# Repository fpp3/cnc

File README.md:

# cnc
Trabajo Practico Integrador de 4to año de la carrera Ingeniería Electrónica en la Universidad Tecnológica Nacional, Facultad Regional Córdoba. Materias involucradas: Electrónica Aplicada II, Técnicas Digitales II, Maquinas e Instalaciones Electricas

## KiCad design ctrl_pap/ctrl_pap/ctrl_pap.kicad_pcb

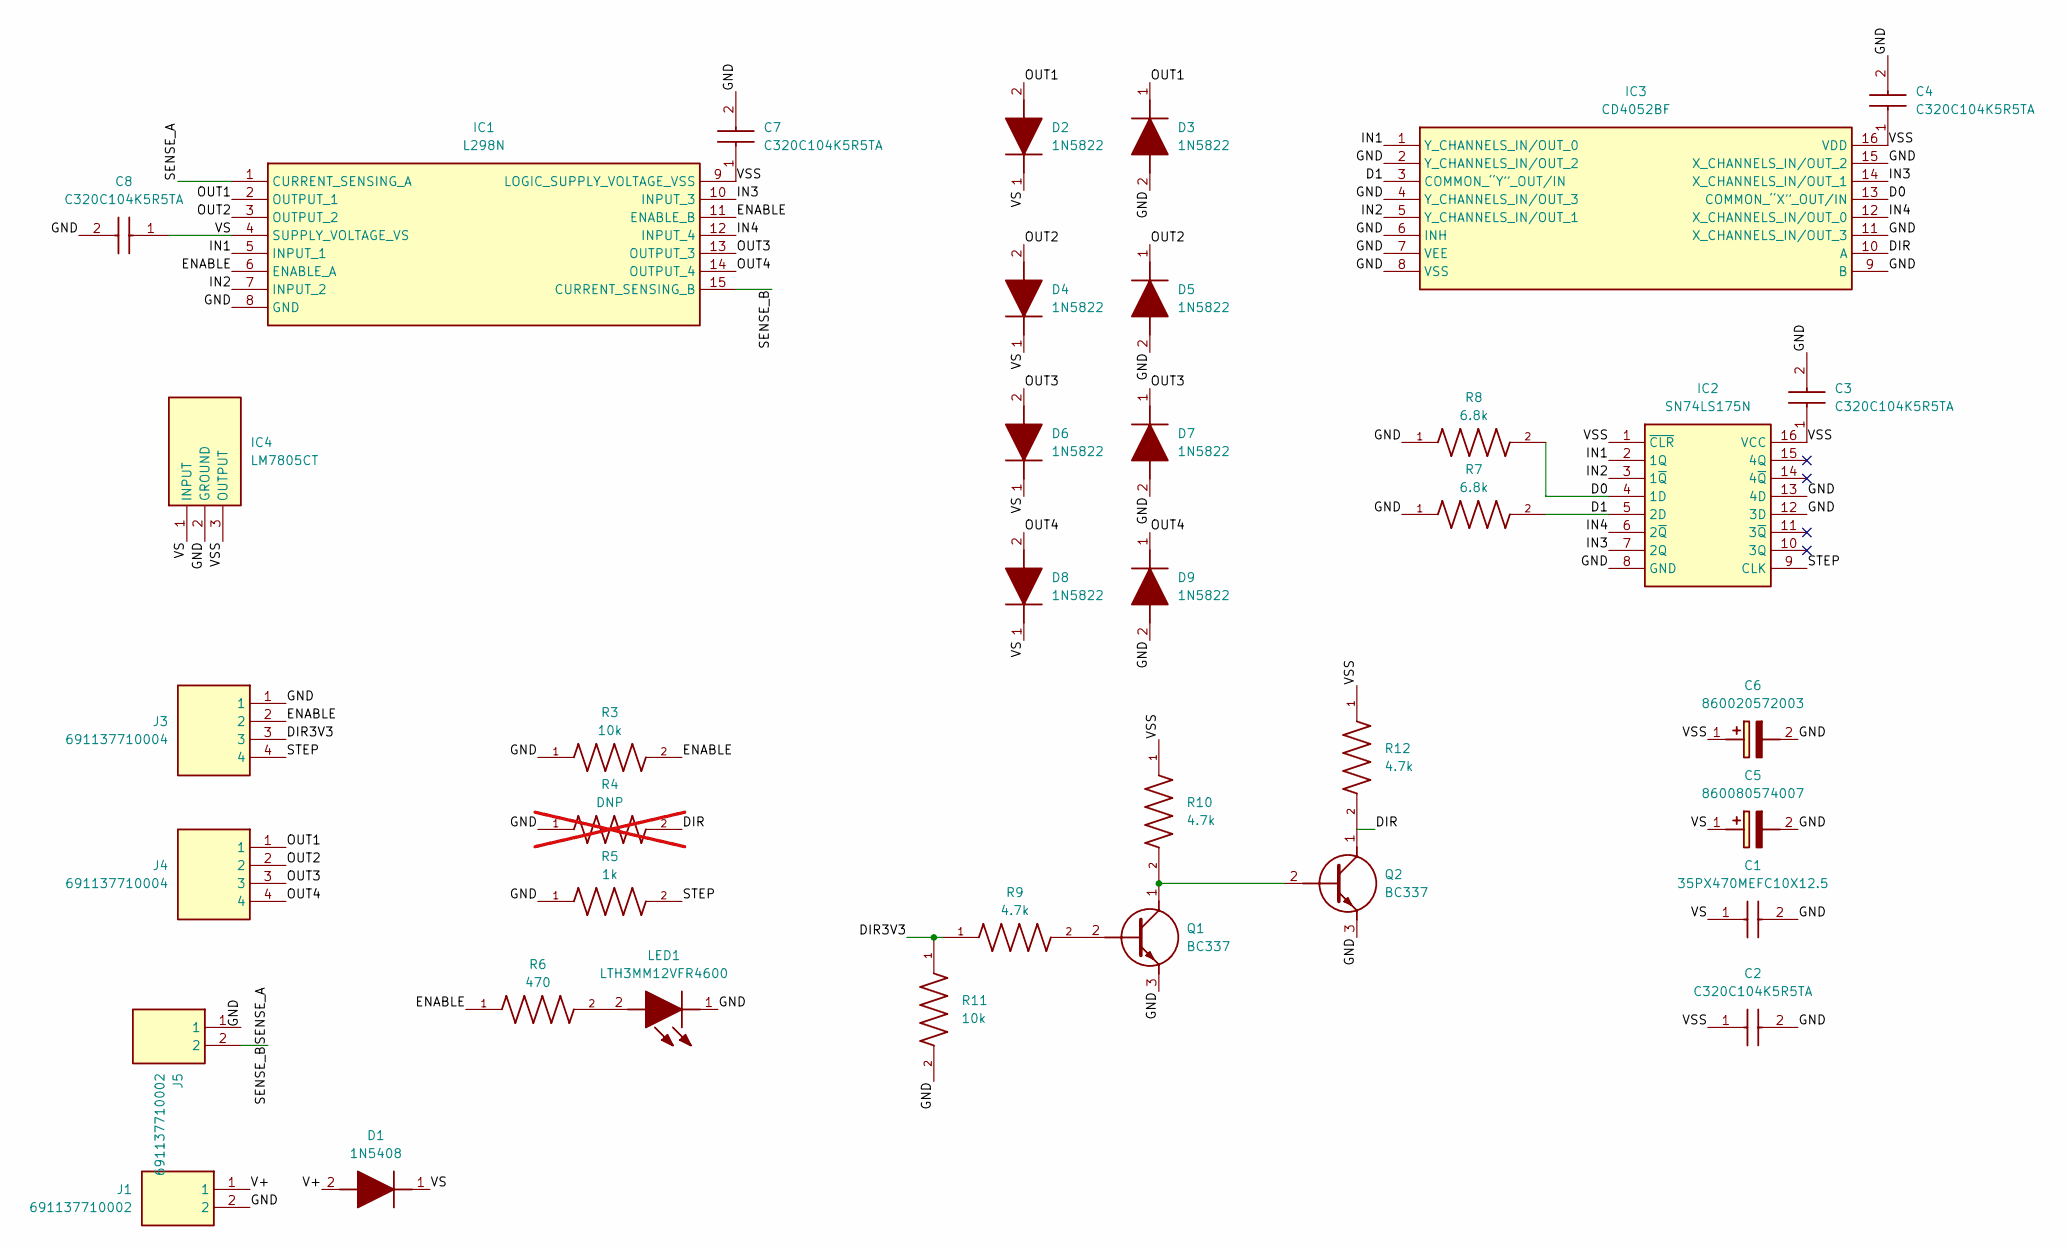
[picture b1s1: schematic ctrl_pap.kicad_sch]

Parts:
C1: 35PX470MEFC10X12.5; CAPPRD500W60D1025H1400; Manufacturer_Part_Number 35PX470MEFC10X12.5; Mouser Part Number 232-35PX470MEFC10X12
C2, C3, C4, C7, C8: C320C104K5R5TA; Manufacturer_Part_Number C320C104K5R5TA; Mouser Part Number 80-C320C104K5R
C5: 860080574007; CAPPRD350W52D800H1300; Manufacturer_Part_Number 860080574007; Mouser Part Number 710-860080574007
C6: 860020572003; CAPPRD200W52D500H1250; Manufacturer_Part_Number 860020572003; Mouser Part Number 710-860020572003
D1: 1N5408; DIOAD2510W125L750D440; Manufacturer_Part_Number 1N5408; Mouser Part Number 637-1N5408
D2, D3, D4, D5, D6, D7, D8, D9: 1N5822; DIOAD3070W130L950D530; Manufacturer_Part_Number 1N5822; Mouser Part Number 512-1N5822
IC1: L298N; TO127P500X2020X2210-15P; Manufacturer_Part_Number L298N; Mouser Part Number 511-L298
IC2: SN74LS175N; DIP794W53P254L1930H508Q16N; Manufacturer_Part_Number SN74LS175N; Mouser Part Number 595-SN74LS175N
IC3: CD4052BF; CDIP762W66P254L2134H508Q16; Manufacturer_Part_Number CD4052BF; Mouser Part Number 595-CD4052BF
IC4: LM7805CT; TO254P470X1028X1955-3P; Manufacturer_Part_Number LM7805CT; Mouser Part Number 926-LM7805CT
J1, J5: 691137710002; SHDR2W70P0X500_1X2_1000X750X1150P; Manufacturer_Part_Number 691137710002; Mouser Part Number 710-691137710002
J3, J4: 691137710004; Manufacturer_Part_Number 691137710004; Mouser Part Number 710-691137710004
LED1: LTH3MM12VFR4600; Manufacturer_Part_Number LTH3MM12VFR4600; Mouser Part Number 593-LTH3MM12VFR4600
Q1, Q2: BC337; Manufacturer_Part_Number BC337
R3, R11: 10k; RESAD1100W55L680D260; PARTREV 201304
R4: DNP; RESAD1100W55L680D260; PARTREV 201304; not fitted
R5: 1k; RESAD1100W55L680D260; PARTREV 201304
R6: 470; RESAD1100W55L680D260; PARTREV 201304
R7, R8: 6.8k; RESAD1100W55L680D260; PARTREV 201304
R9, R10, R12: 4.7k; RESAD1100W55L680D260; PARTREV 201304

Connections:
/D0: IC2.4 (1D), IC3.13 (COMMON_“X”_OUT/IN), R8.2
/D1: IC2.5 (2D), IC3.3 (COMMON_“Y”_OUT/IN), R7.2
/DIR: IC3.10 (A), Q2.1 (C), R4.2, R12.2
/DIR3V3: J3.3, R9.1, R11.1
/ENABLE: IC1.6 (ENABLE_A), IC1.11 (ENABLE_B), J3.2, R3.2, R6.1
/GND: C1.2 (-), C2.2, C3.2, C4.2, C5.2 (-), C6.2 (-), C7.2, C8.2, D3.2 (A), D5.2 (A), D7.2 (A), D9.2 (A), IC1.8 (GND), IC2.8 (GND), IC2.12 (3D), IC2.13 (4D), IC3.2 (Y_CHANNELS_IN/OUT_2), IC3.4 (Y_CHANNELS_IN/OUT_3), IC3.6 (INH), IC3.7 (VEE), IC3.8 (VSS), IC3.9 (B), IC3.11 (X_CHANNELS_IN/OUT_3), IC3.15 (X_CHANNELS_IN/OUT_2), IC4.2 (GROUND), J1.2, J3.1, J5.1, LED1.1 (K), Q1.3 (E), Q2.3 (E), R3.1, R4.1, R5.1, R7.1, R8.1, R11.2
/IN1: IC1.5 (INPUT_1), IC2.2 (1Q), IC3.1 (Y_CHANNELS_IN/OUT_0)
/IN2: IC1.7 (INPUT_2), IC2.3 (1~Q), IC3.5 (Y_CHANNELS_IN/OUT_1)
/IN3: IC1.10 (INPUT_3), IC2.7 (2Q), IC3.14 (X_CHANNELS_IN/OUT_1)
/IN4: IC1.12 (INPUT_4), IC2.6 (2~Q), IC3.12 (X_CHANNELS_IN/OUT_0)
/OUT1: D2.2 (A), D3.1 (K), IC1.2 (OUTPUT_1), J4.1
/OUT2: D4.2 (A), D5.1 (K), IC1.3 (OUTPUT_2), J4.2
/OUT3: D6.2 (A), D7.1 (K), IC1.13 (OUTPUT_3), J4.3
/OUT4: D8.2 (A), D9.1 (K), IC1.14 (OUTPUT_4), J4.4
/SENSE_A: IC1.1 (CURRENT_SENSING_A), IC1.15 (CURRENT_SENSING_B), J5.2
/STEP: IC2.9 (CLK), J3.4, R5.2
/V+: D1.2 (A), J1.1
/VS: C1.1 (+), C5.1 (+), C8.1, D1.1 (K), D2.1 (K), D4.1 (K), D6.1 (K), D8.1 (K), IC1.4 (SUPPLY_VOLTAGE_VS), IC4.1 (INPUT)
/VSS: C2.1, C3.1, C4.1, C6.1 (+), C7.1, IC1.9 (LOGIC_SUPPLY_VOLTAGE_VSS), IC2.1 (~CLR), IC2.16 (VCC), IC3.16 (VDD), IC4.3 (OUTPUT), R10.1, R12.1
unnamed: LED1.2 (A), R6.2
unnamed: Q1.2 (B), R9.2
unnamed: Q1.1 (C), Q2.2 (B), R10.2

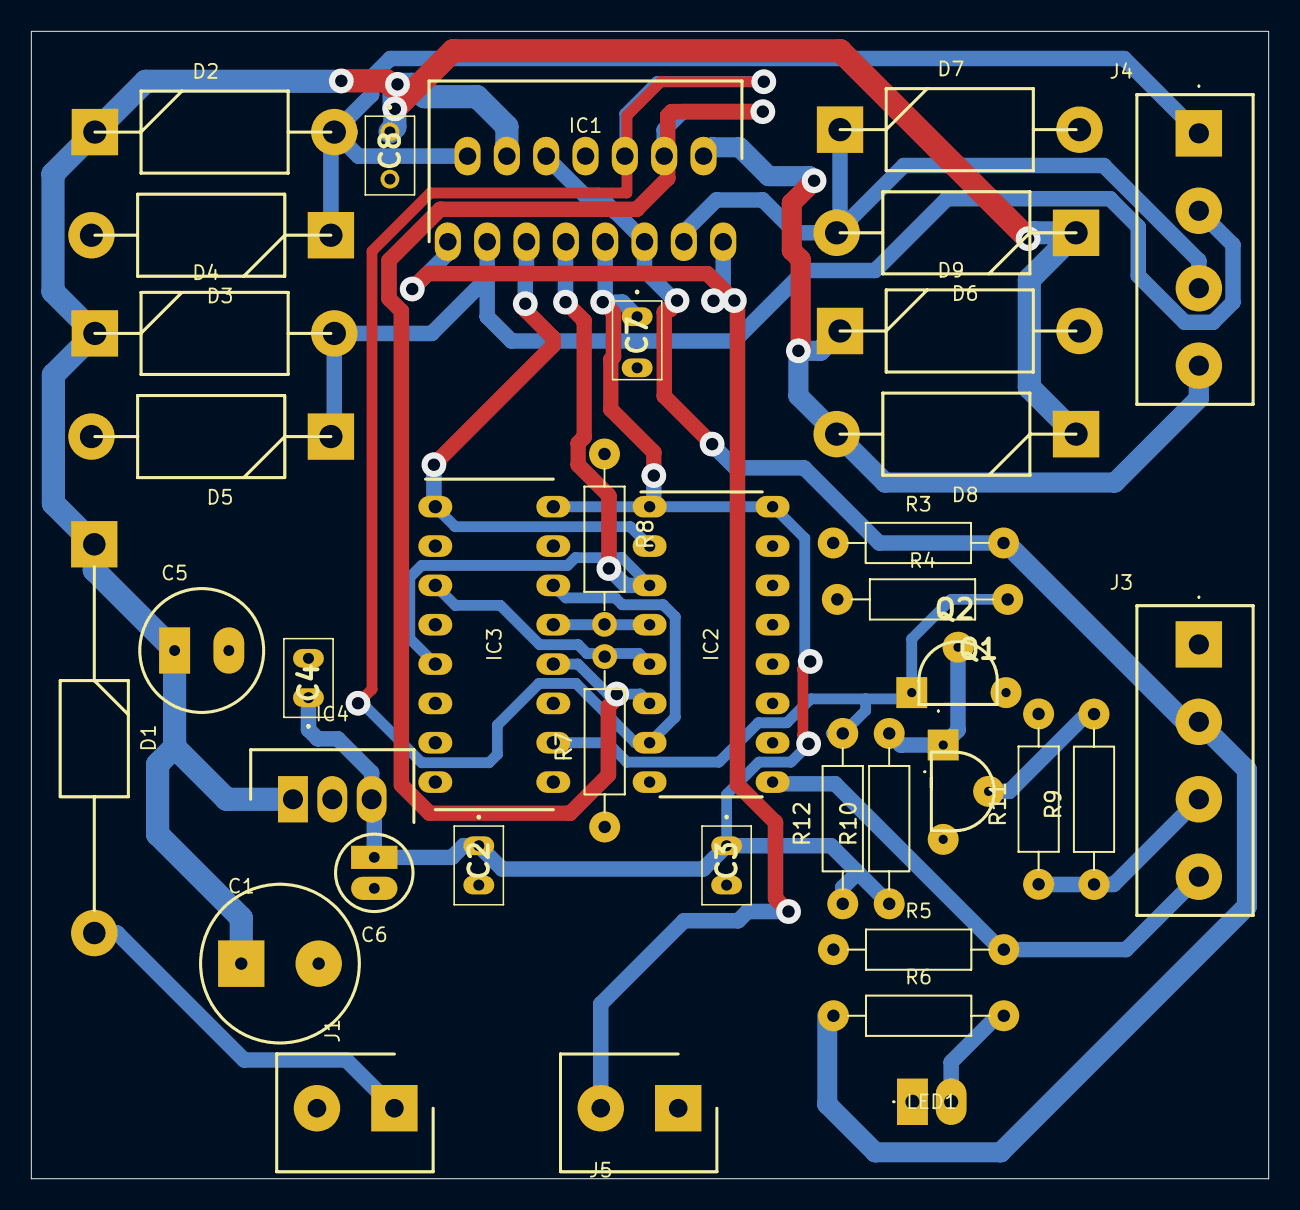
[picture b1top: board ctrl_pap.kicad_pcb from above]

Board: 2 copper layers, 79.9 x 74.1 mm, 38 parts (0 on the bottom side), 22 nets.

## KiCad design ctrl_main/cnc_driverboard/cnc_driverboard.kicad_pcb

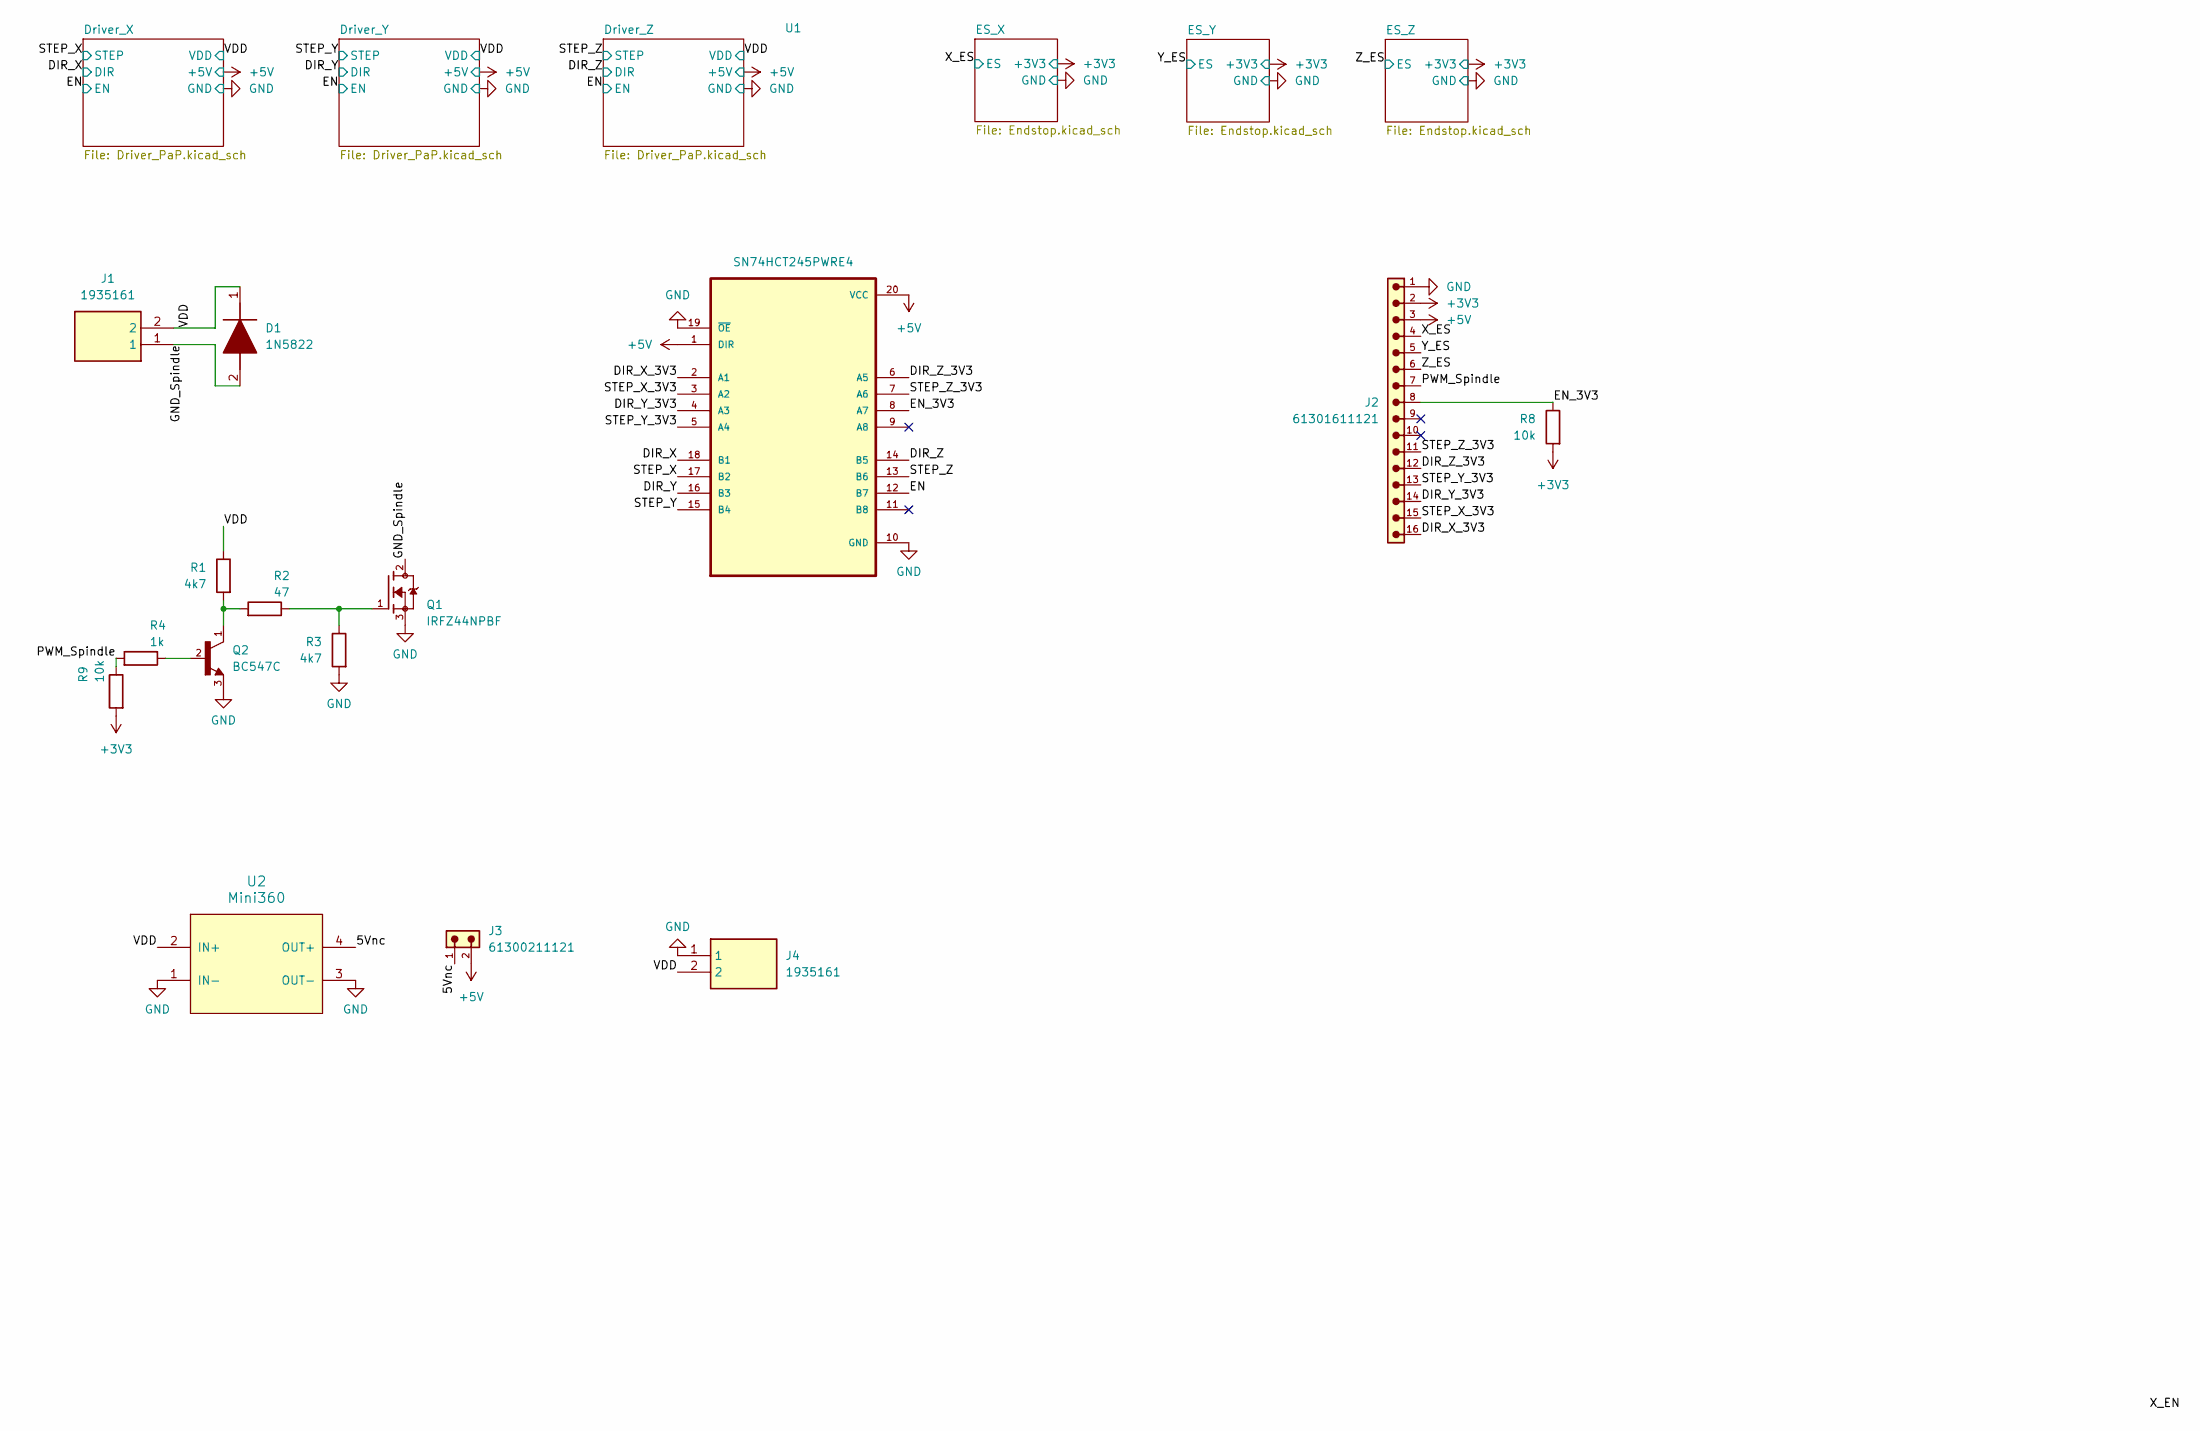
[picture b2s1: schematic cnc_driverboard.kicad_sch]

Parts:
D1: 1N5822; DIOAD3070W130L950D530; Manufacturer_Part_Number 1N5822; Mouser Part Number 512-1N5822
J1, J4: 1935161; Manufacturer_Part_Number 1935161; Mouser Part Number 651-1935161
J2: 61301611121; MPN 61301611121
J3: 61300211121; MPN 61300211121
Q1: IRFZ44NPBF; TO254P1016X419X2286-3; MPN IRFZ44NPBF
Q2: BC547C; TRANS_BC547C; MPN BC547C
R1, R3: 4k7; R_Axial_DIN0207_L6.3mm_D2.5mm_P7.62mm_Horizontal
R2: 47; R_Axial_DIN0207_L6.3mm_D2.5mm_P7.62mm_Horizontal
R4: 1k; R_Axial_DIN0207_L6.3mm_D2.5mm_P7.62mm_Horizontal
R8: 10k; R_Axial_DIN0207_L6.3mm_D2.5mm_P15.24mm_Horizontal
R9: 10k; R_Axial_DIN0207_L6.3mm_D2.5mm_P7.62mm_Horizontal
U1: SN74HCT245PWRE4; SOP65P640X120-20N; MPN SN74HCT245PWRE4
U2: Mini360; Mini360_step-down

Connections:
+3V3: J2.2, R8.2, R9.2; also elsewhere on the board
+5V: J2.3, J3.2, U1.1 (DIR), U1.20 (VCC); also elsewhere on the board
/5Vnc: J3.1, U2.4 (OUT+)
/DIR_X: U1.18 (B1); also elsewhere on the board
/DIR_X_3V3: J2.16, U1.2 (A1)
/DIR_Y: U1.16 (B3); also elsewhere on the board
/DIR_Y_3V3: J2.14, U1.4 (A3)
/DIR_Z: U1.14 (B5); also elsewhere on the board
/DIR_Z_3V3: J2.12, U1.6 (A5)
/EN: U1.12 (B7); also elsewhere on the board
/EN_3V3: J2.8, R8.1, U1.8 (A7)
/GND_Spindle: D1.2 (A), J1.1, Q1.2
/PWM_Spindle: J2.7, R4.2, R9.1
/STEP_X: U1.17 (B2); also elsewhere on the board
/STEP_X_3V3: J2.15, U1.3 (A2)
/STEP_Y: U1.15 (B4); also elsewhere on the board
/STEP_Y_3V3: J2.13, U1.5 (A4)
/STEP_Z: U1.13 (B6); also elsewhere on the board
/STEP_Z_3V3: J2.11, U1.7 (A6)
/VDD: D1.1 (K), J1.2, J4.2, R1.1, U2.2 (IN+); also elsewhere on the board
/X_ES: J2.4; also elsewhere on the board
/Y_ES: J2.5; also elsewhere on the board
/Z_ES: J2.6; also elsewhere on the board
GND: J2.1, J4.1, Q1.3, Q2.3, R3.2, U1.10 (GND), U1.19 (~OE), U2.1 (IN-), U2.3 (OUT-); also elsewhere on the board
unnamed: Q1.1, R2.1, R3.1
unnamed: Q2.1, R1.2, R2.2
unnamed: Q2.2, R4.1

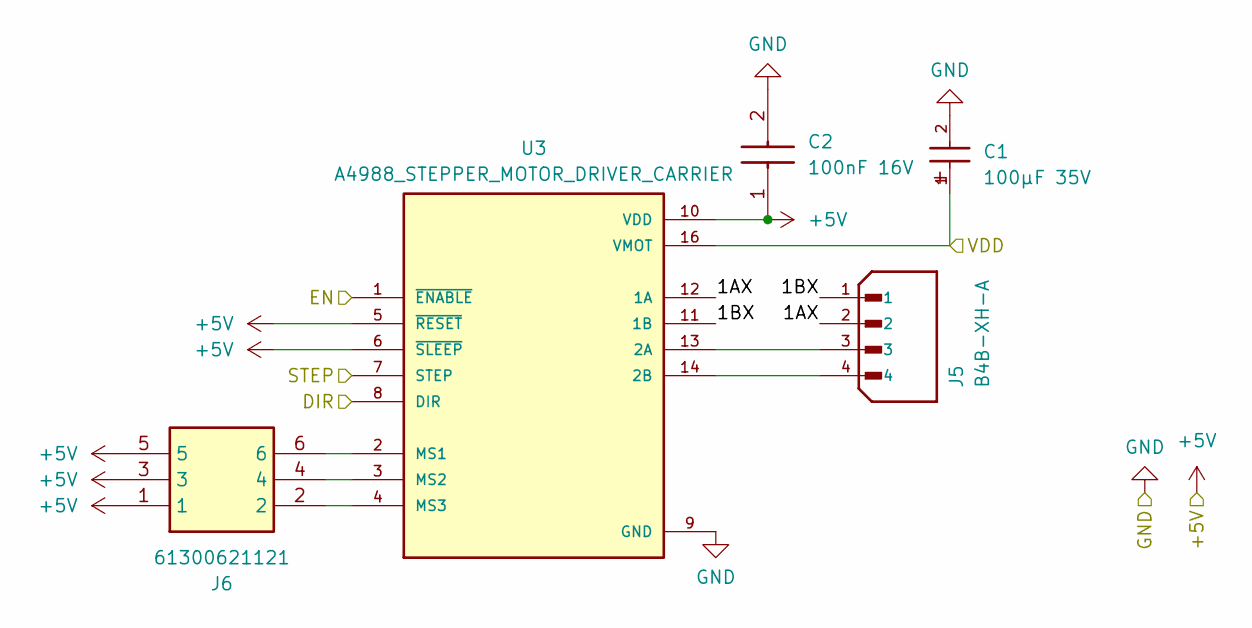
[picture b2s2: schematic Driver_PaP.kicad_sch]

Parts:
C1: 100µF 35V; WCAP-ATUL_6.3X11_DXL_; MPN WCAP-ATUL_6.3X11
C2: 100nF 16V; CAPC2012X95N; MPN CC0805KRX7R7BB104; Mouser Part Number 603-CC805KRX7R7BB104
J5: B4B-XH-A; JST_B4B-XH-A; MPN B4B-XH-A
J6: 61300621121; HDRV6W64P254_2X3_762X508X889P; Manufacturer_Part_Number 61300621121; Mouser Part Number 710-61300621121
U3: A4988_STEPPER_MOTOR_DRIVER_CARRIER; MODULE_A4988_STEPPER_MOTOR_DRIVER_CARRIER; MPN A4988 STEPPER MOTOR DRIVER CARRIER

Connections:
+5V: C2.1, J6.1, J6.3, J6.5, U3.5 (~RESET), U3.6 (~SLEEP), U3.10 (VDD); also elsewhere on the board
/DIR_X: U3.8 (DIR); also elsewhere on the board
/Driver_X/1AX: J5.2, U3.12 (1A)
/Driver_X/1BX: J5.1, U3.11 (1B)
/EN: U3.1 (~ENABLE); also elsewhere on the board
/STEP_X: U3.7 (STEP); also elsewhere on the board
/VDD: C1.1, U3.16 (VMOT); also elsewhere on the board
GND: C1.2, C2.2, U3.9 (GND), U3.15 (GND); also elsewhere on the board
unnamed: J5.3, U3.13 (2A)
unnamed: J5.4, U3.14 (2B)
unnamed: J6.6, U3.2 (MS1)
unnamed: J6.4, U3.3 (MS2)
unnamed: J6.2, U3.4 (MS3)

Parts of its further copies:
C3, C5: 100µF 35V; WCAP-ATUL_6.3X11_DXL_; MPN WCAP-ATUL_6.3X11
C4, C6: 100nF 16V; CAPC2012X95N; MPN CC0805KRX7R7BB104; Mouser Part Number 603-CC805KRX7R7BB104
J7, J9: B4B-XH-A; JST_B4B-XH-A; MPN B4B-XH-A
J8, J10: 61300621121; HDRV6W64P254_2X3_762X508X889P; Manufacturer_Part_Number 61300621121; Mouser Part Number 710-61300621121
U4, U5: A4988_STEPPER_MOTOR_DRIVER_CARRIER; MODULE_A4988_STEPPER_MOTOR_DRIVER_CARRIER; MPN A4988 STEPPER MOTOR DRIVER CARRIER

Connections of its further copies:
+5V: C4.1, C6.1, J8.1, J8.3, J8.5, J10.1, J10.3, J10.5, U4.5 (~RESET), U4.6 (~SLEEP), U4.10 (VDD), U5.5 (~RESET), U5.6 (~SLEEP), U5.10 (VDD); also elsewhere on the board
/DIR_Y: U4.8 (DIR); also elsewhere on the board
/DIR_Z: U5.8 (DIR); also elsewhere on the board
/Driver_Y/1AX: J7.2, U4.12 (1A)
/Driver_Y/1BX: J7.1, U4.11 (1B)
/Driver_Z/1AX: J9.2, U5.12 (1A)
/Driver_Z/1BX: J9.1, U5.11 (1B)
/EN: U4.1 (~ENABLE), U5.1 (~ENABLE); also elsewhere on the board
/STEP_Y: U4.7 (STEP); also elsewhere on the board
/STEP_Z: U5.7 (STEP); also elsewhere on the board
/VDD: C3.1, C5.1, U4.16 (VMOT), U5.16 (VMOT); also elsewhere on the board
GND: C3.2, C4.2, C5.2, C6.2, U4.9 (GND), U4.15 (GND), U5.9 (GND), U5.15 (GND); also elsewhere on the board
unnamed: J7.3, U4.13 (2A)
unnamed: J7.4, U4.14 (2B)
unnamed: J8.6, U4.2 (MS1)
unnamed: J8.4, U4.3 (MS2)
unnamed: J8.2, U4.4 (MS3)
unnamed: J9.3, U5.13 (2A)
unnamed: J9.4, U5.14 (2B)
unnamed: J10.6, U5.2 (MS1)
unnamed: J10.4, U5.3 (MS2)
unnamed: J10.2, U5.4 (MS3)

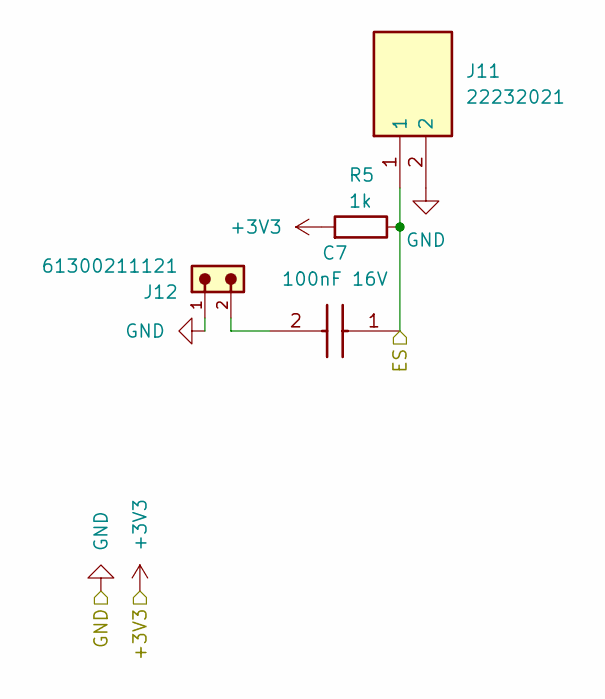
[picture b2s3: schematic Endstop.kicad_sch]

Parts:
C7: 100nF 16V; CAPC2012X95N; MPN CC0805KRX7R7BB104; Mouser Part Number 603-CC805KRX7R7BB104
J11: 22232021; CONN_A-6373-02A_MOL; Manufacturer_Part_Number 1935161; Mouser Part Number 651-1935161
J12: 61300211121; MPN 61300211121
R5: 1k; R_Axial_DIN0207_L6.3mm_D2.5mm_P7.62mm_Horizontal

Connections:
+3V3: R5.2; also elsewhere on the board
/X_ES: C7.1, J11.1, R5.1; also elsewhere on the board
GND: J11.2, J12.1; also elsewhere on the board
unnamed: C7.2, J12.2

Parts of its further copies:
C8, C9: 100nF 16V; CAPC2012X95N; MPN CC0805KRX7R7BB104; Mouser Part Number 603-CC805KRX7R7BB104
J13, J15: 22232021; CONN_A-6373-02A_MOL; Manufacturer_Part_Number 1935161; Mouser Part Number 651-1935161
J14, J16: 61300211121; MPN 61300211121
R6, R7: 1k; R_Axial_DIN0207_L6.3mm_D2.5mm_P7.62mm_Horizontal

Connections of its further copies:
+3V3: R6.2, R7.2; also elsewhere on the board
/Y_ES: C8.1, J13.1, R6.1; also elsewhere on the board
/Z_ES: C9.1, J15.1, R7.1; also elsewhere on the board
GND: J13.2, J14.1, J15.2, J16.1; also elsewhere on the board
unnamed: C8.2, J14.2
unnamed: C9.2, J16.2

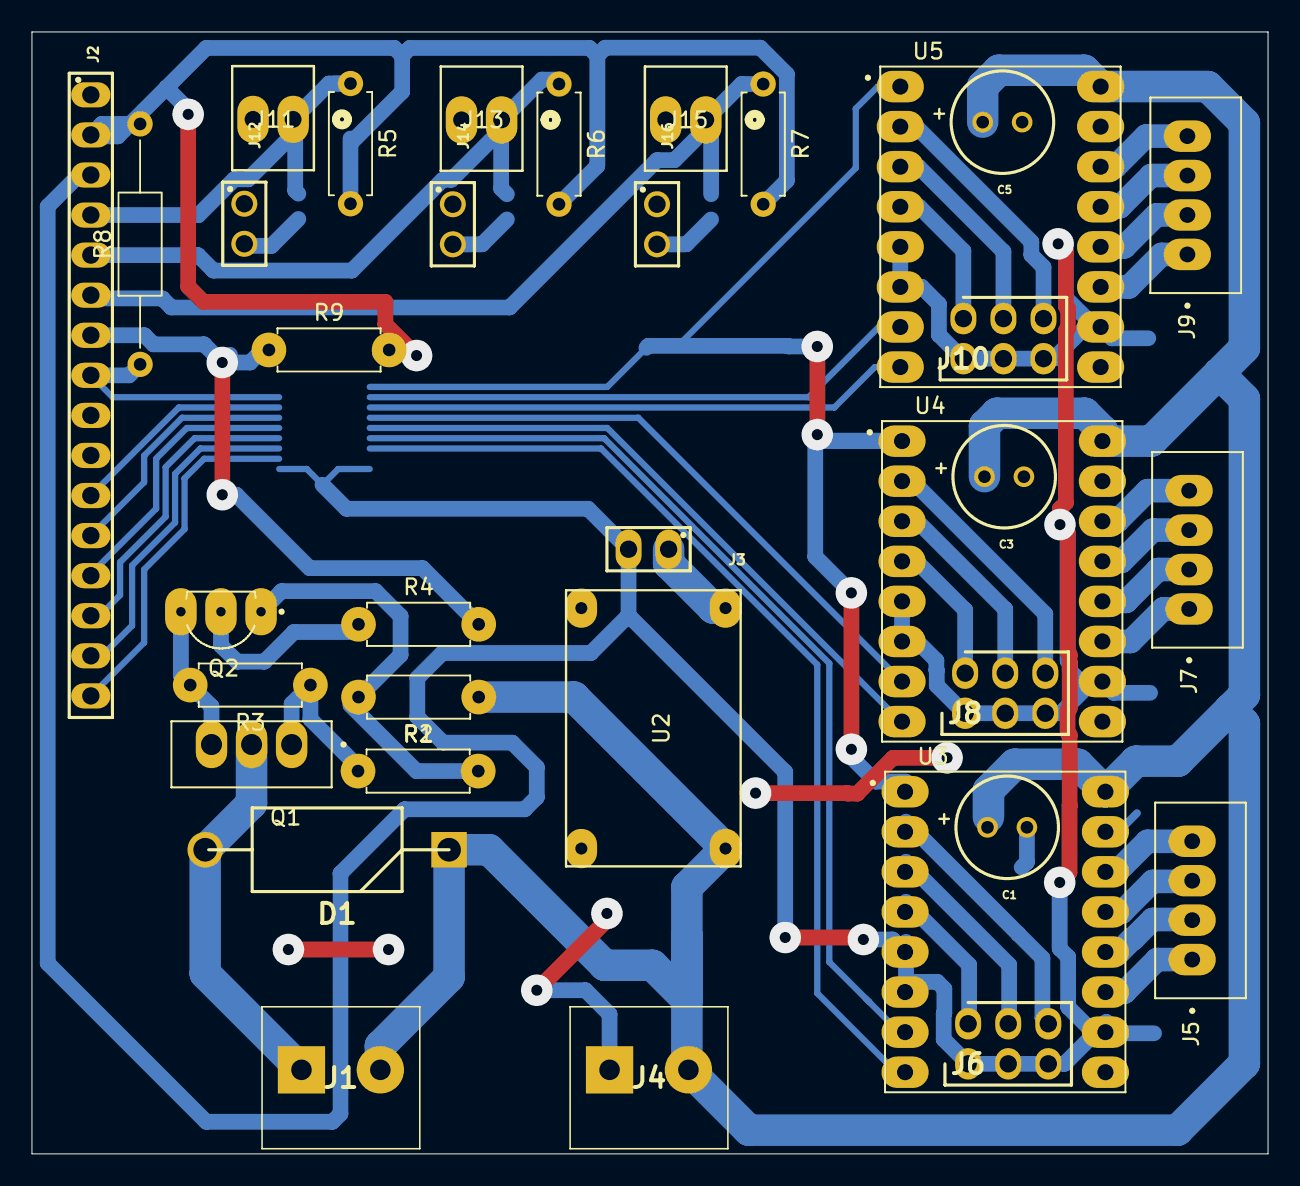
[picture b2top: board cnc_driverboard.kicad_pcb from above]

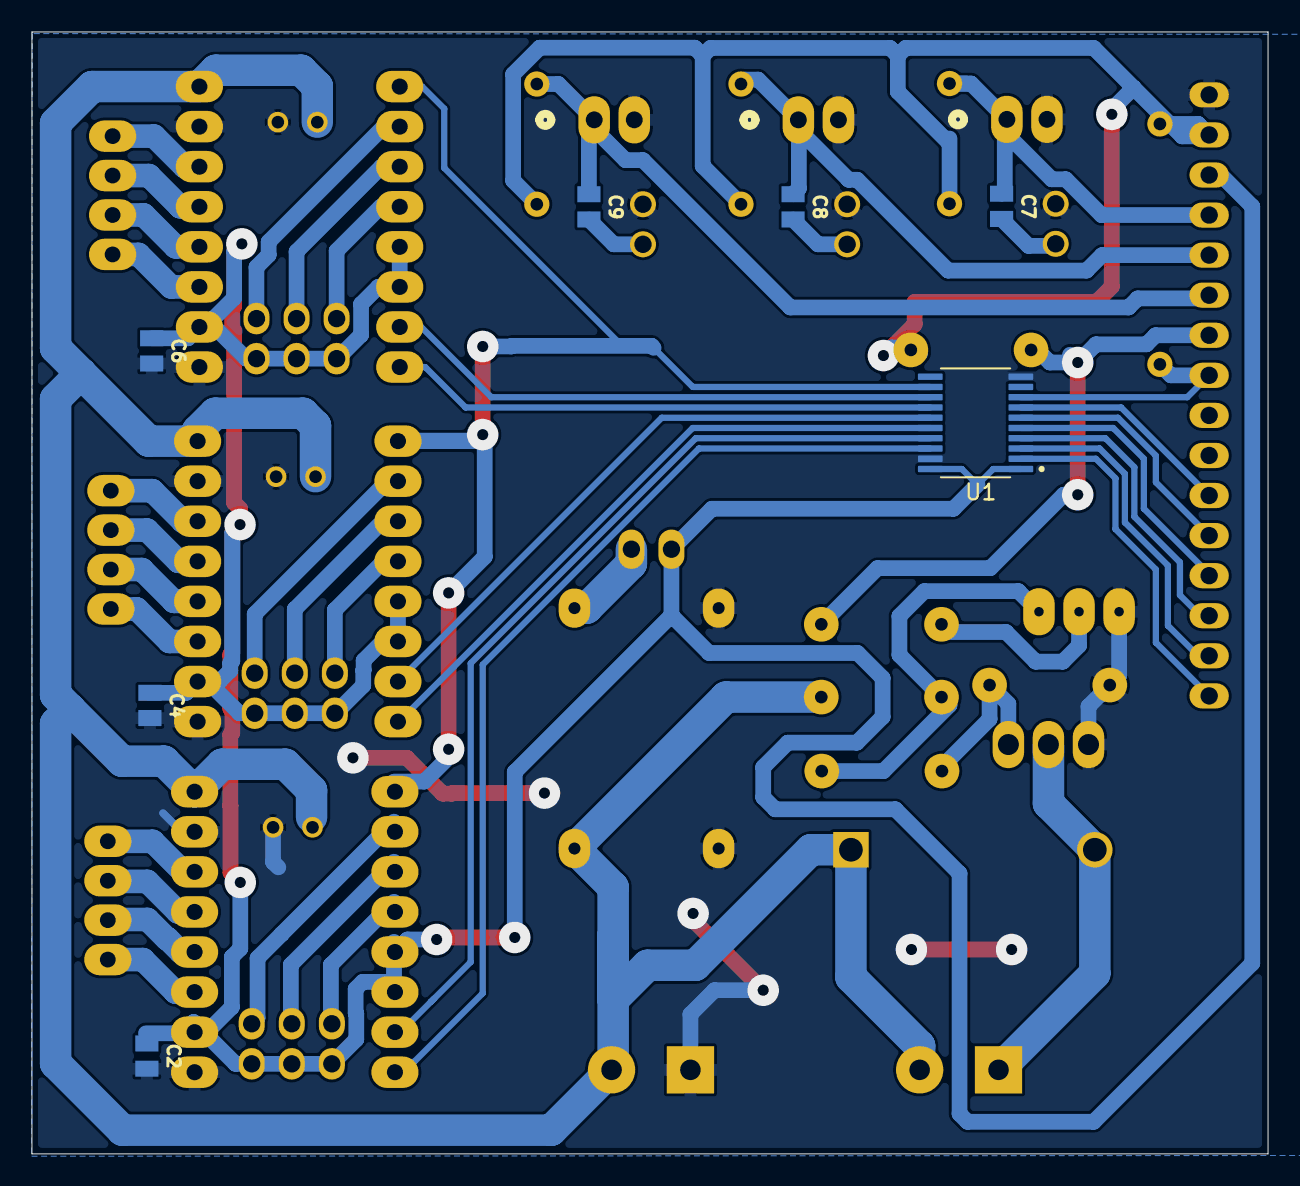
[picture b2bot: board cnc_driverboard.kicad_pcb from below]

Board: 2 copper layers, 78.4 x 71.1 mm, 42 parts (7 on the bottom side), 51 nets.

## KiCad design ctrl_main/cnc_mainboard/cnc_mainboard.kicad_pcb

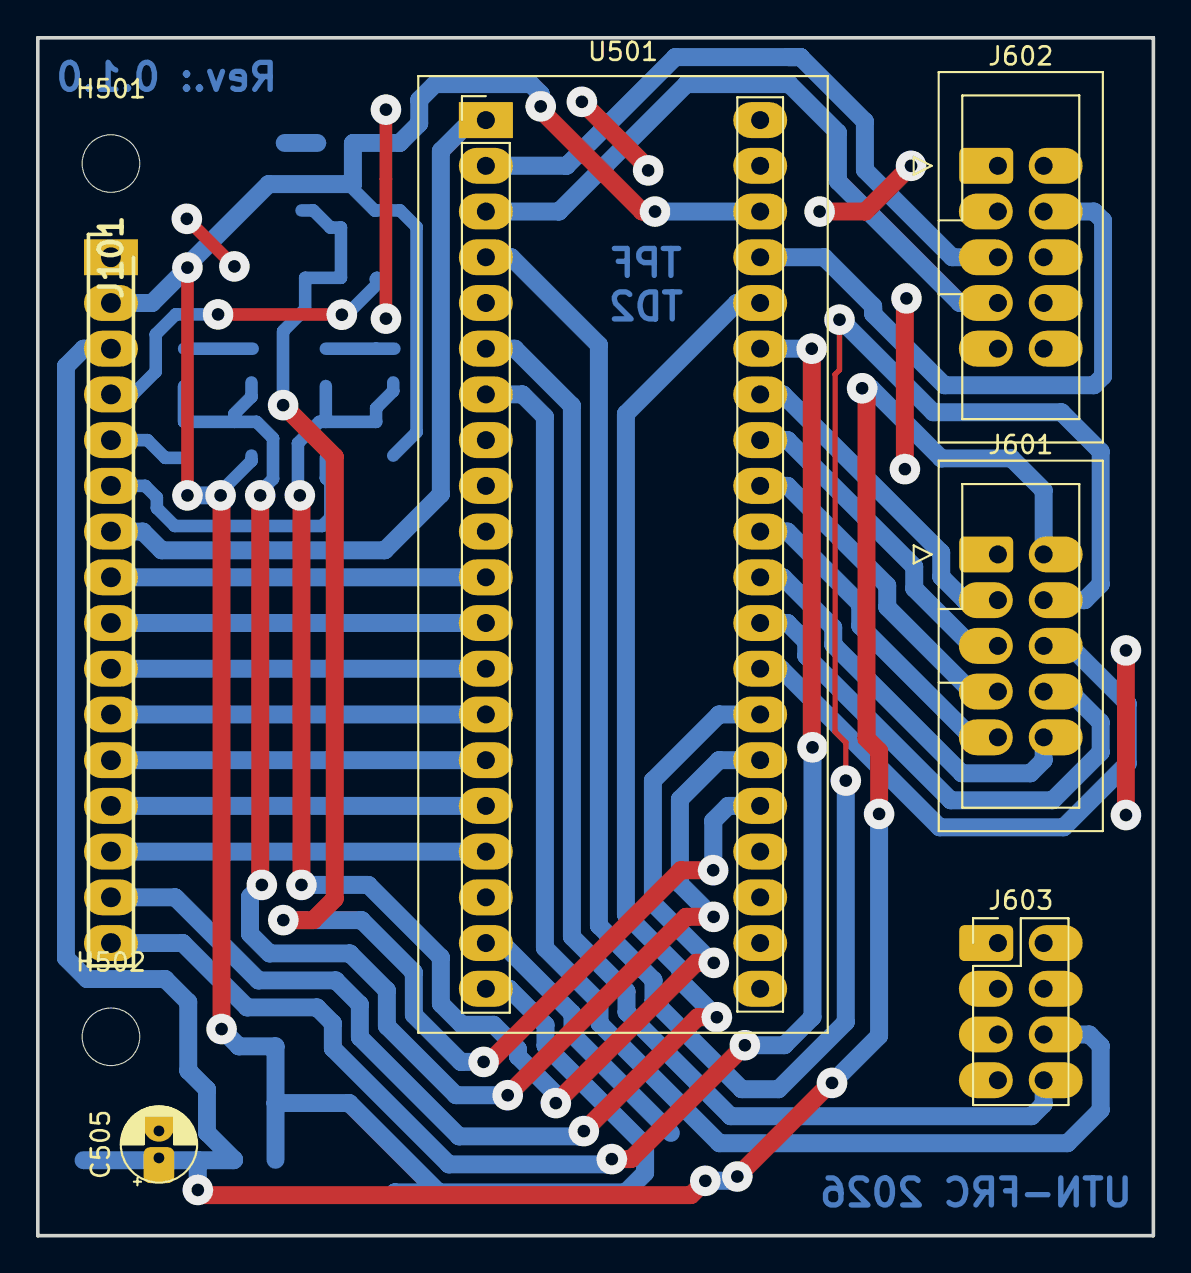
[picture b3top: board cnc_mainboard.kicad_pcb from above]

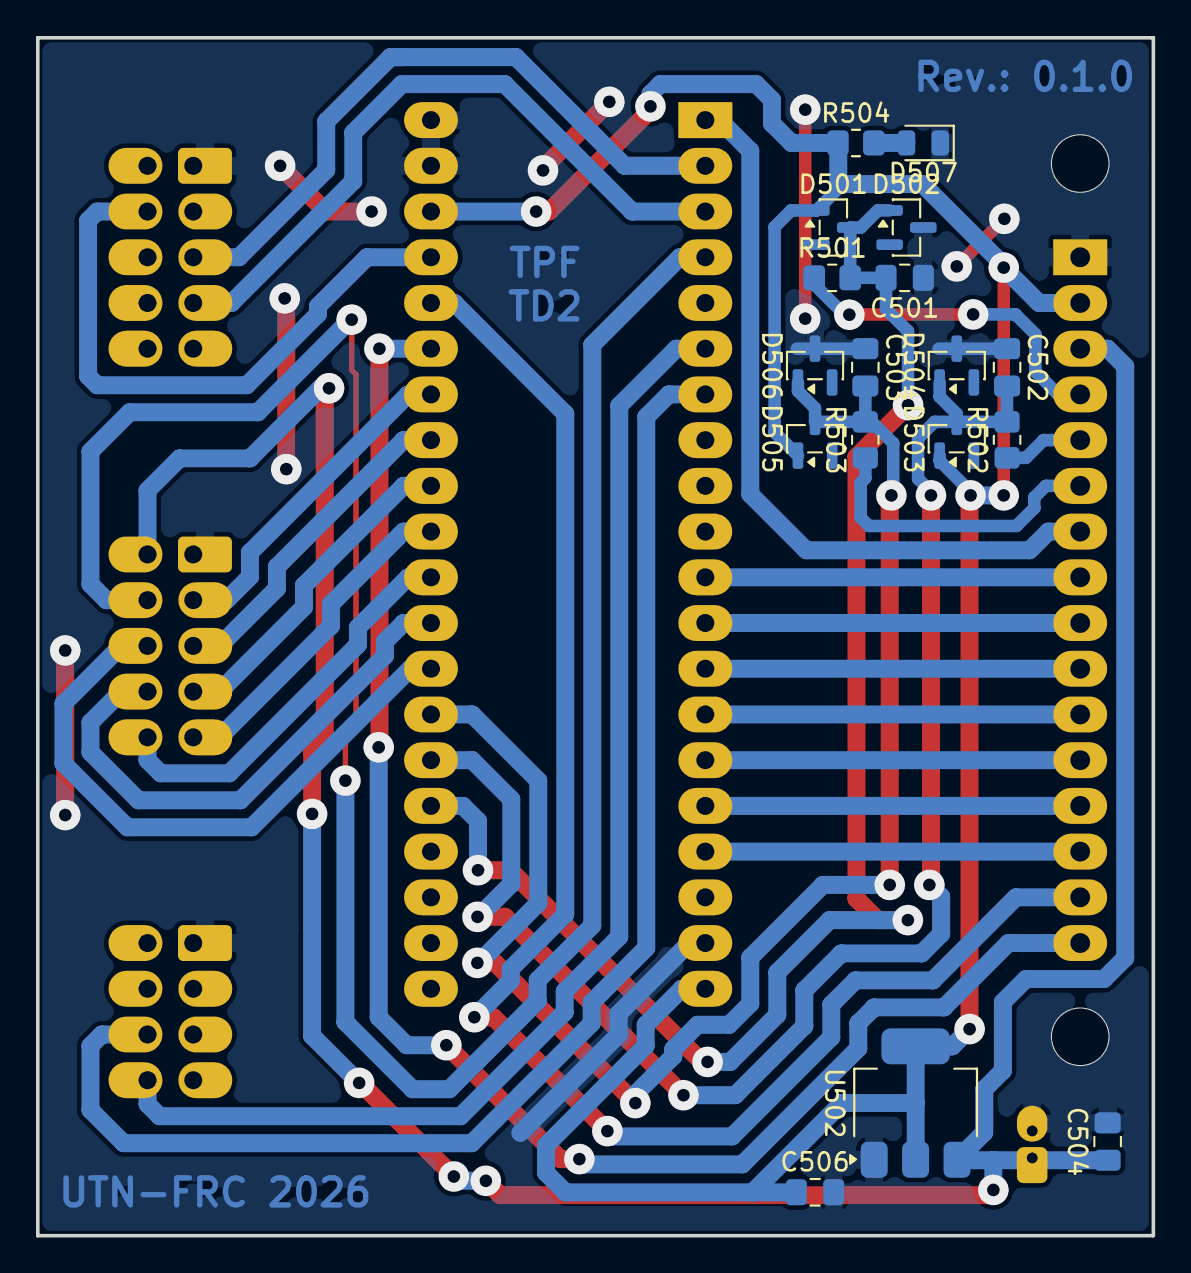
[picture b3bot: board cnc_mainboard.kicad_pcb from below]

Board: 2 copper layers, 62.0 x 66.5 mm, 25 parts (17 on the bottom side), 33 nets.

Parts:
C501, C502, C503, C504: 100n; C_0805_2012Metric_Pad1.18x1.45mm_HandSolder
C505: 10u; CP_Radial_D4.0mm_P1.50mm
C506: 22u; C_0805_2012Metric_Pad1.18x1.45mm_HandSolder
D501, D502, D503, D504, D505, D506: BAT54W; SOT-23
D507: LED; LED_0805_2012Metric
H501, H502: MountingHole; MountingHole_3.2mm_M3
J101: PH1-16-UA; HDRV16W64P0X254_1X16_4064X250X847P
J601, J602: Conn_02x05_Odd_Even; IDC-Header_2x05_P2.54mm_Vertical
J603: Conn_02x04_Odd_Even; PinHeader_2x04_P2.54mm_Vertical
R501, R502, R503: 10K; R_0805_2012Metric_Pad1.20x1.40mm_HandSolder
R504: 330; R_0805_2012Metric_Pad1.20x1.40mm_HandSolder
U501: YAAJ_BluePill; YAAJ_BluePill_2
U502: AMS1117-3.3; SOT-223-3_TabPin2

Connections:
/Core Board Bluepill/+3V3: C506.1, D501.1 (A), D503.1 (A), D505.1 (A), J101.2, R504.1, U501.20 (3V3), U501.38 (3V3), U502.2 (VO)
/Core Board Bluepill/+5V: C504.1, C505.1, J101.3, J601.2, U502.3 (VI)
/Core Board Bluepill/EXT_X_END: J101.4, R501.1
/Core Board Bluepill/EXT_Y_END: J101.5, R502.1
/Core Board Bluepill/EXT_Z_END: J101.6, R503.1
/Core Board Bluepill/GND: C501.1, C502.1, C503.1, C504.2, C505.2, C506.2, D502.3 (K), D504.3 (K), D506.3 (K), D507.1 (K), J101.1, J601.1, J602.1, J603.1, U501.19 (GND), U501.39 (GND), U501.40 (GND), U502.1 (GND)
/Core Board Bluepill/GPIO0: J601.6, U501.28 (PA3)
/Core Board Bluepill/GPIO1: J601.8, U501.29 (PA4)
/Core Board Bluepill/GPIO2: J601.10, U501.30 (PA5)
/Core Board Bluepill/GPIO3: J601.9, U501.31 (PA6)
/Core Board Bluepill/GPIO4: J601.7, U501.32 (PA7)
/Core Board Bluepill/GPIO5: J601.5, U501.33 (PB0)
/Core Board Bluepill/GPIO6: J601.3, U501.34 (PB1)
/Core Board Bluepill/GPIO7: J602.5, U501.2 (PB13)
/Core Board Bluepill/GPIO8: J602.7, U501.3 (PB14)
/Core Board Bluepill/GPIO9: J601.4, U501.4 (PB15)
/Core Board Bluepill/RESET: J602.4, U501.37 (RST)
/Core Board Bluepill/SPINDLE_PWM: J101.7, U501.1 (PB12)
/Core Board Bluepill/USART1_RX: J603.6, U501.7 (PA10)
/Core Board Bluepill/USART1_TX: J603.8, U501.6 (PA9)
/Core Board Bluepill/X_DIR: J101.9, U501.12 (PB4)
/Core Board Bluepill/X_EN: J101.8, U501.11 (PB3)
/Core Board Bluepill/X_END: C501.2, D501.3 (K), D502.1 (A), R501.2, U501.25 (PA0)
/Core Board Bluepill/X_STEP: J101.10, U501.13 (PB5)
/Core Board Bluepill/Y_DIR: J101.12, U501.15 (PB7)
/Core Board Bluepill/Y_EN: J101.11, U501.14 (PB6)
/Core Board Bluepill/Y_END: C502.2, D503.3 (K), D504.1 (A), R502.2, U501.26 (PA1)
/Core Board Bluepill/Y_STEP: J101.13, U501.16 (PB8)
/Core Board Bluepill/Z_DIR: J101.15, U501.36 (PB11)
/Core Board Bluepill/Z_EN: J101.14, U501.17 (PB9)
/Core Board Bluepill/Z_END: C503.2, D505.3 (K), D506.1 (A), R503.2, U501.27 (PA2)
/Core Board Bluepill/Z_STEP: J101.16, U501.35 (PB10)
unnamed: D507.2 (A), R504.2
